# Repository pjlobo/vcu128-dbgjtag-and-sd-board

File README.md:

# vcu128-dbgjtag-and-sd-board
A companion board for the Xilinx VCU128 Evaluation Kit that adds an SD Card reader, a 10-pin JTAG header and a pushbutton

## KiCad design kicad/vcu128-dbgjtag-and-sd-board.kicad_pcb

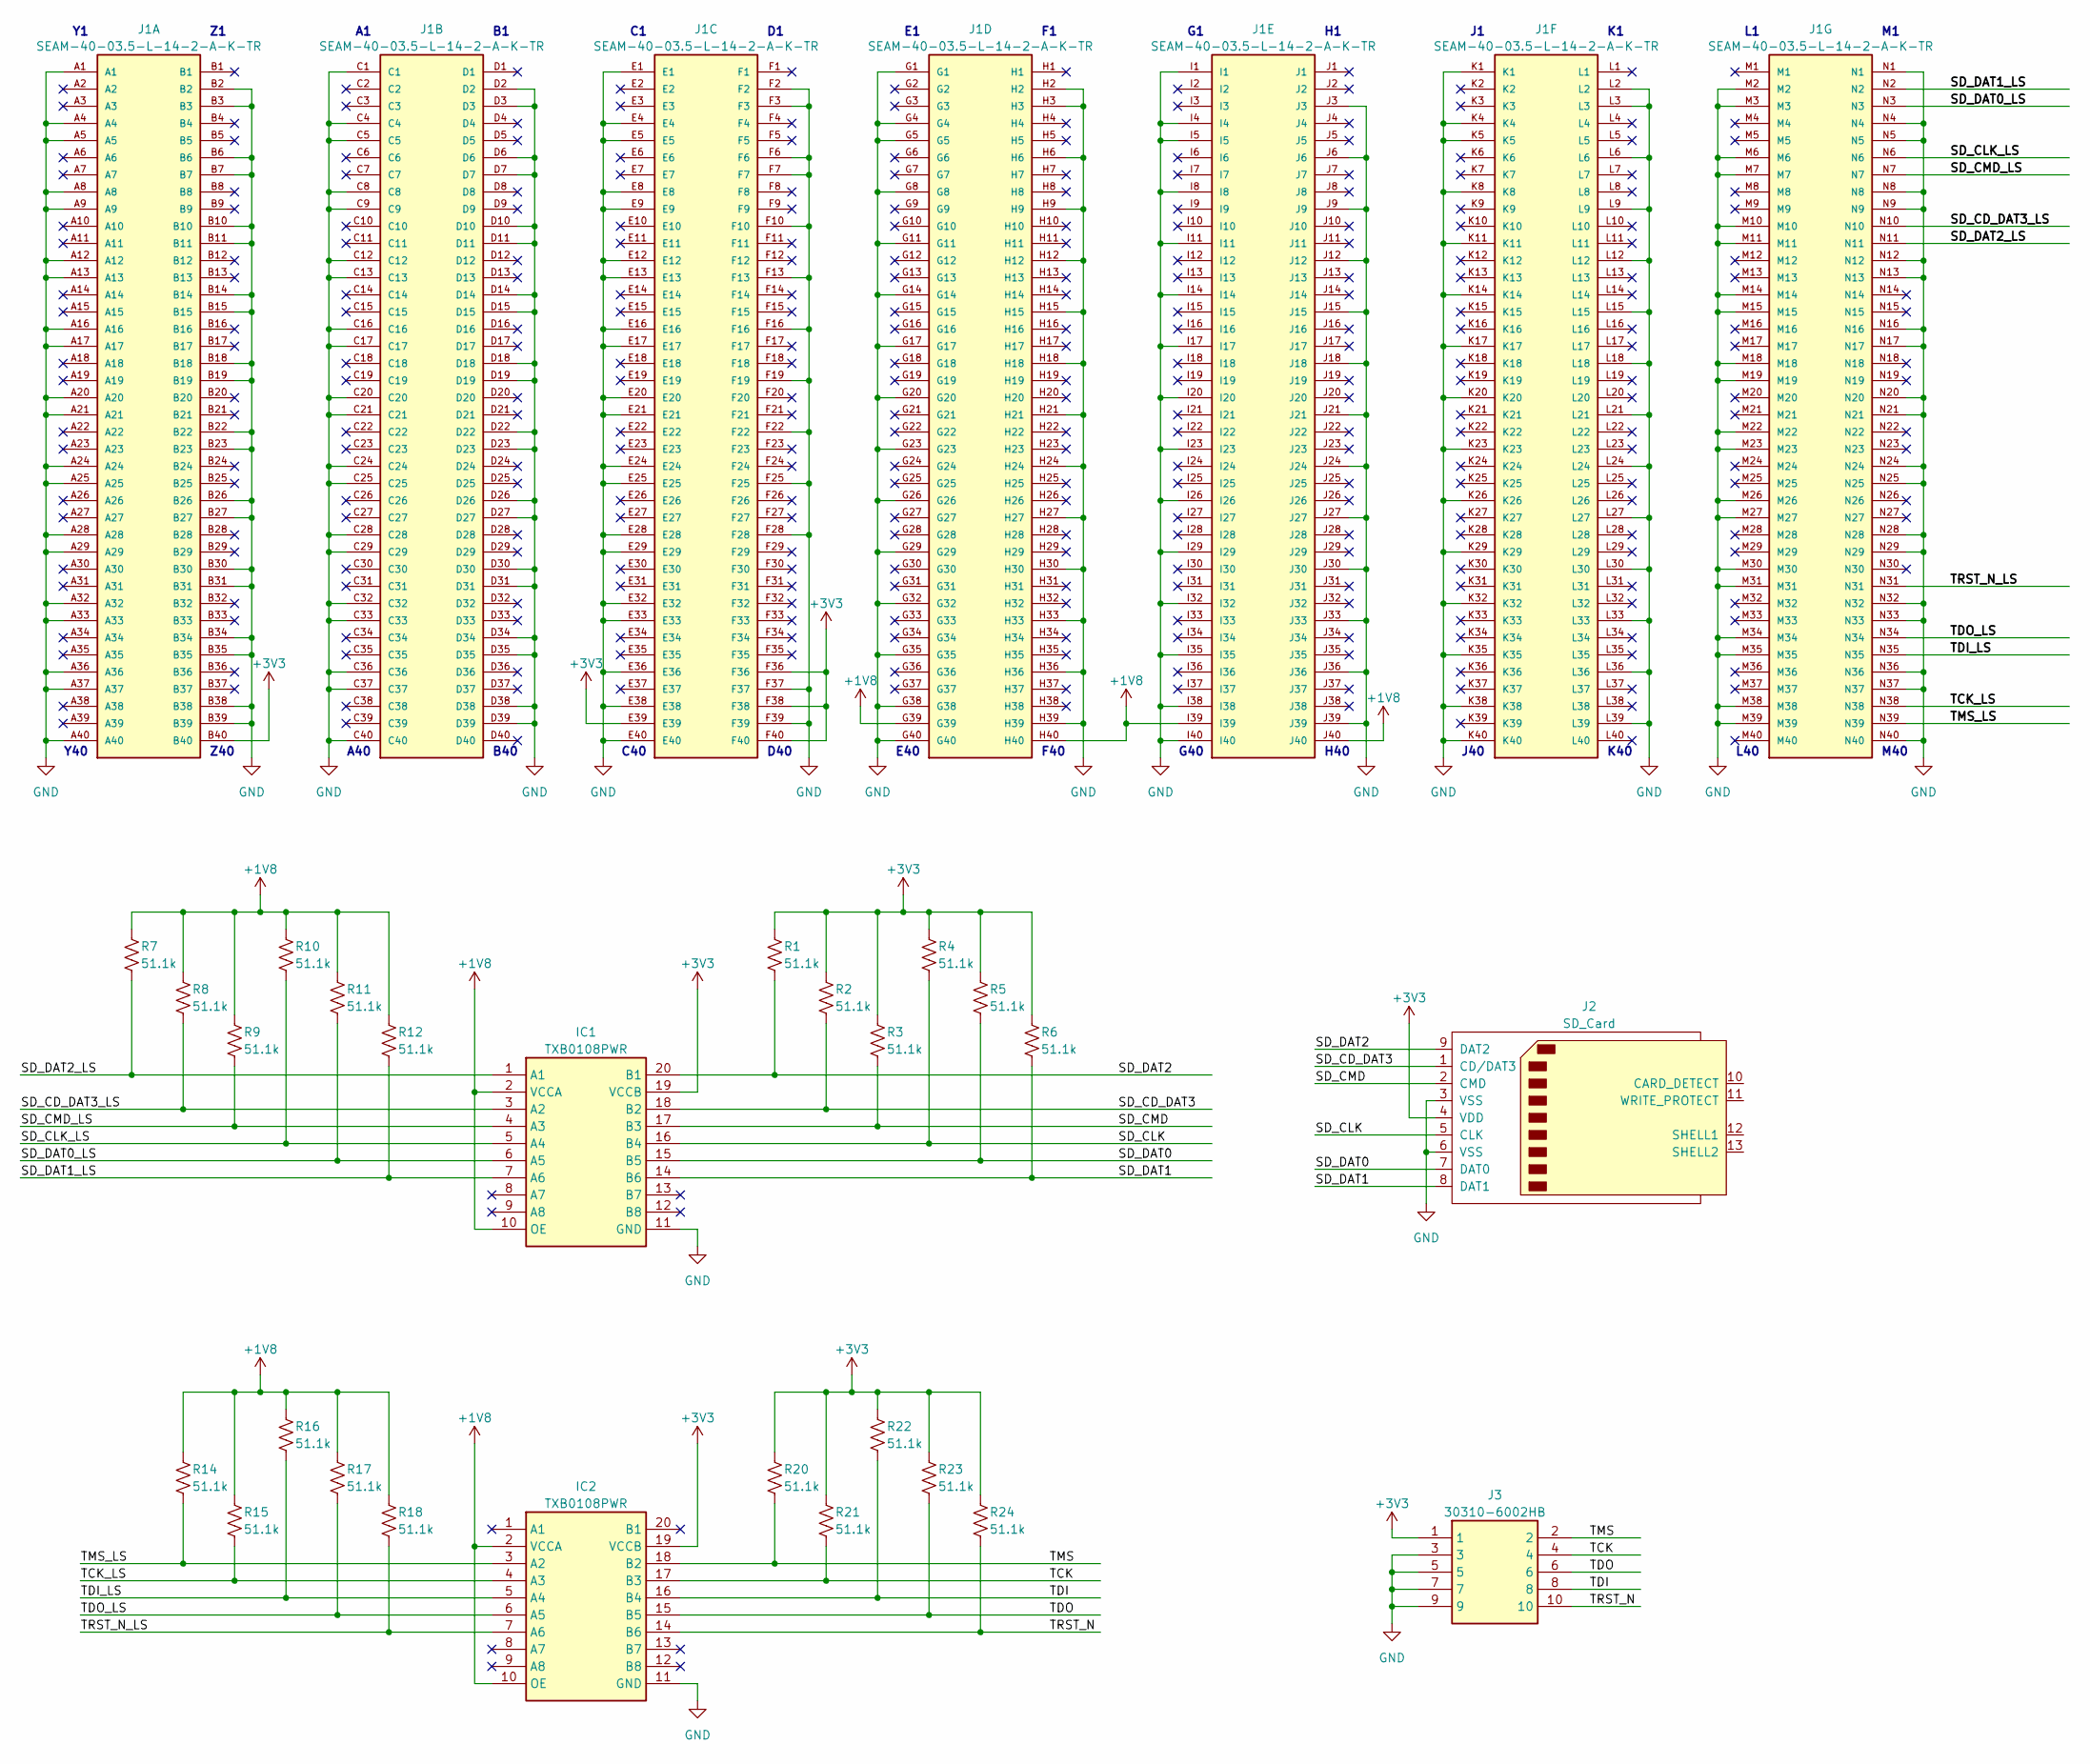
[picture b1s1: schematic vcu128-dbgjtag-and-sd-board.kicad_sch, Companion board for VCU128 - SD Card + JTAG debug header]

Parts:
IC1, IC2: TXB0108PWR; SOP65P640X120-20N; Manufacturer_Part_Number TXB0108PWR
J1: SEAM-40-03.5-L-14-2-A-K-TR; SAMTEC_SEAM-40-03.5-L-14-2-A-K-TR
J2: SD_Card; DM1AA-SF-PEJ_21__1
J3: 30310-6002HB; SHDR10W64P254_2X5_2030X878X930P; Manufacturer_Part_Number 30310-6002HB
R1, R2, R3, R4, R5, R6, R7, R8, R9, R10, R11, R12, R14, R15, R16, R17, R18, R20, R21, R22, R23, R24: 51.1k; R_0603_1608Metric

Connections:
+1V8: IC1.2 (VCCA), IC1.10 (OE), IC2.2 (VCCA), IC2.10 (OE), J1.G39, J1.H40, J1.I39, J1.J40, R7.1, R8.1, R9.1, R10.1, R11.1, R12.1, R14.1, R15.1, R16.1, R17.1, R18.1
+3V3: IC1.19 (VCCB), IC2.19 (VCCB), J1.B40, J1.E39, J1.F36, J1.F38, J1.F40, J2.4 (VDD), J3.1, R1.1, R2.1, R3.1, R4.1, R5.1, R6.1, R20.1, R21.1, R22.1, R23.1, R24.1
/SD_CD_DAT3: IC1.18 (B2), J2.1 (CD/DAT3), R2.2
/SD_CD_DAT3_LS: IC1.3 (A2), J1.N10, R8.2
/SD_CLK: IC1.16 (B4), J2.5 (CLK), R4.2
/SD_CLK_LS: IC1.5 (A4), J1.N6, R10.2
/SD_CMD: IC1.17 (B3), J2.2 (CMD), R3.2
/SD_CMD_LS: IC1.4 (A3), J1.N7, R9.2
/SD_DAT0: IC1.15 (B5), J2.7 (DAT0), R5.2
/SD_DAT0_LS: IC1.6 (A5), J1.N3, R11.2
/SD_DAT1: IC1.14 (B6), J2.8 (DAT1), R6.2
/SD_DAT1_LS: IC1.7 (A6), J1.N2, R12.2
/SD_DAT2: IC1.20 (B1), J2.9 (DAT2), R1.2
/SD_DAT2_LS: IC1.1 (A1), J1.N11, R7.2
/TCK: IC2.17 (B3), J3.4, R21.2
/TCK_LS: IC2.4 (A3), J1.N38, R15.2
/TDI: IC2.16 (B4), J3.8, R22.2
/TDI_LS: IC2.5 (A4), J1.N35, R16.2
/TDO: IC2.15 (B5), J3.6, R23.2
/TDO_LS: IC2.6 (A5), J1.N34, R17.2
/TMS: IC2.18 (B2), J3.2, R20.2
/TMS_LS: IC2.3 (A2), J1.N39, R14.2
/TRST_N: IC2.14 (B6), J3.10, R24.2
/TRST_N_LS: IC2.7 (A6), J1.N31, R18.2
GND: IC1.11 (GND), IC2.11 (GND), J1.A1, J1.A4, J1.A5, J1.A8, J1.A9, J1.A12, J1.A13, J1.A16, J1.A17, J1.A20, J1.A21, J1.A24, J1.A25, J1.A28, J1.A29, J1.A32, J1.A33, J1.A36, J1.A37, J1.A40, J1.B2, J1.B3, J1.B6, J1.B7, J1.B10, J1.B11, J1.B14, J1.B15, J1.B18, J1.B19, J1.B22, J1.B23, J1.B26, J1.B27, J1.B30, J1.B31, J1.B34, J1.B35, J1.B38, J1.B39, J1.C1, J1.C4, J1.C5, J1.C8, J1.C9, J1.C12, J1.C13, J1.C16, J1.C17, J1.C20, J1.C21, J1.C24, J1.C25, J1.C28, J1.C29, J1.C32, J1.C33, J1.C36, J1.C37, J1.C40, J1.D2, J1.D3, J1.D6, J1.D7, J1.D10, J1.D11, J1.D14, J1.D15, J1.D18, J1.D19, J1.D22, J1.D23, J1.D26, J1.D27, J1.D30, J1.D31, J1.D34, J1.D35, J1.D38, J1.D39, J1.E1, J1.E4, J1.E5, J1.E8, J1.E9, J1.E12, J1.E13, J1.E16, J1.E17, J1.E20, J1.E21, J1.E24, J1.E25, J1.E28, J1.E29, J1.E32, J1.E33, J1.E36, J1.E38, J1.E40, J1.F2, J1.F3, J1.F6, J1.F7, J1.F10, J1.F13, J1.F16, J1.F19, J1.F22, J1.F25, J1.F28, J1.F37, J1.F39, J1.G1, J1.G4, J1.G5, J1.G8, J1.G11, J1.G14, J1.G17, J1.G20, J1.G23, J1.G26, J1.G29, J1.G32, J1.G35, J1.G38, J1.G40, J1.H2, J1.H3, J1.H6, J1.H9, J1.H12, J1.H15, J1.H18, J1.H21, J1.H24, J1.H27, J1.H30, J1.H33, J1.H36, J1.H39, J1.I1, J1.I4, J1.I5, J1.I8, J1.I11, J1.I14, J1.I17, J1.I20, J1.I23, J1.I26, J1.I29, J1.I32, J1.I35, J1.I38, J1.I40, J1.J3, J1.J6, J1.J9, J1.J12, J1.J15, J1.J18, J1.J21, J1.J24, J1.J27, J1.J30, J1.J33, J1.J36, J1.J39, J1.K1, J1.K4, J1.K5, J1.K8, J1.K11, J1.K14, J1.K17, J1.K20, J1.K23, J1.K26, J1.K29, J1.K32, J1.K35, J1.K38, J1.K40, J1.L2, J1.L3, J1.L6, J1.L9, J1.L12, J1.L15, J1.L18, J1.L21, J1.L24, J1.L27, J1.L30, J1.L33, J1.L36, J1.L39, J1.M2, J1.M3, J1.M6, J1.M7, J1.M10, J1.M11, J1.M14, J1.M15, J1.M18, J1.M19, J1.M22, J1.M23, J1.M26, J1.M27, J1.M30, J1.M31, J1.M34, J1.M35, J1.M38, J1.M39, J1.N1, J1.N4, J1.N5, J1.N8, J1.N9, J1.N12, J1.N13, J1.N16, J1.N17, J1.N20, J1.N21, J1.N24, J1.N25, J1.N28, J1.N29, J1.N32, J1.N33, J1.N36, J1.N37, J1.N40, J2.3 (VSS), J2.6 (VSS), J3.3, J3.5, J3.7, J3.9

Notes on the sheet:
B40
C40
J40
L40
E40
Z40
M40
A40
K40
H40
Y40
G40
D40
F40

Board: 2 copper layers, 27 parts (1 on the bottom side), 25 nets, no tracks yet.

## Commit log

2023-04-26 Create LICENSE
2023-04-27 Work in progress...
